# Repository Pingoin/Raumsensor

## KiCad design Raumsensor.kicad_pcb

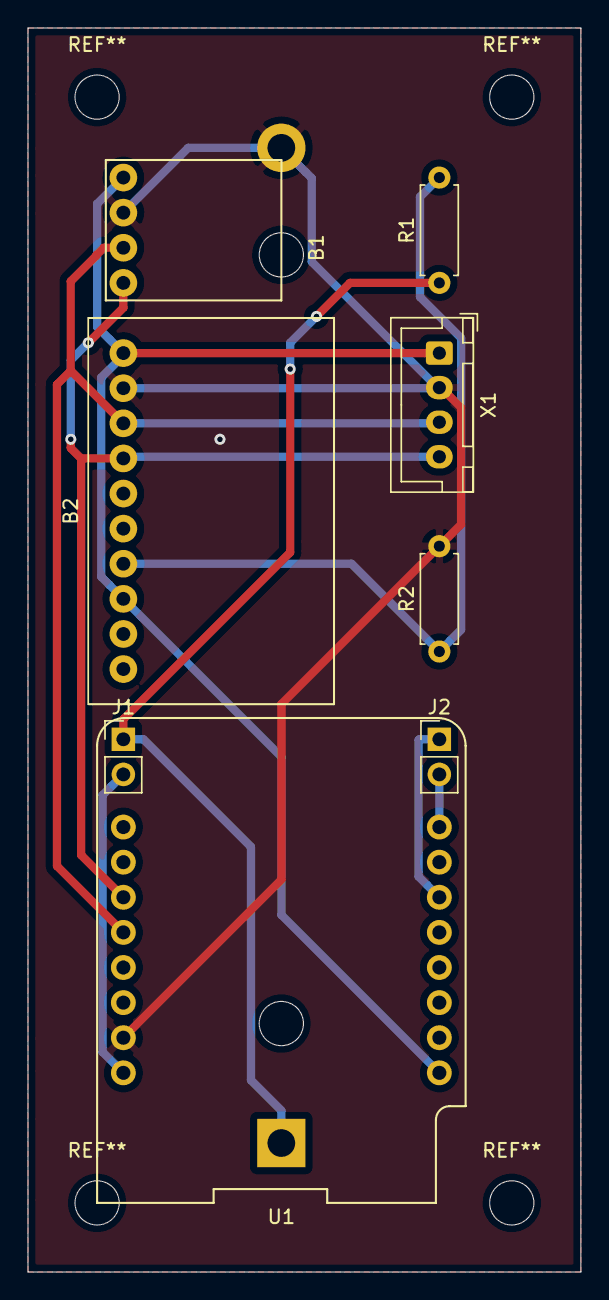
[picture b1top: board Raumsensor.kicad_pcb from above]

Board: 2 copper layers, 40.0 x 90.0 mm, 9 parts (1 on the bottom side), 9 nets.

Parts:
B1: BME28_I2C; BME280_I2C
B2: ADS1115
BT1: Battery; BatteryHolder_MPD_BH-18650-PC2
J1: VCC; PinHeader_1x02_P2.54mm_Vertical
J2: DeepSleep; PinHeader_1x02_P2.54mm_Vertical
R1: 180K; R_Axial_DIN0207_L6.3mm_D2.5mm_P7.62mm_Horizontal
R2: 330K; R_Axial_DIN0207_L6.3mm_D2.5mm_P7.62mm_Horizontal
U1: WeMos_mini; wemos-d1-mini
X1: I2C; JST_XH_B4B-XH-A_1x04_P2.50mm_Vertical

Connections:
+3V3: B1.1, B2.1, B2.8, U1.16, X1.1
/SCL: B1.4, B2.4, U1.6, X1.4
/SDA: B1.3, B2.3, U1.5, X1.3
GND: B1.2, B2.2, BT1.2, R2.2, U1.2, X1.2
unnamed: B2.7, R1.2, R2.1
unnamed: J1.2, U1.1
unnamed: J2.1, U1.11
unnamed: J2.2, U1.9
VCC: BT1.1, J1.1, R1.1

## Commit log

2019-11-29 init
2019-11-29 main nachgeschickt
2019-12-03 Umstieg OTA auf MQTT
2019-12-04 I2C Pins angepasst
2019-12-05 Bibliotheken optimiert
